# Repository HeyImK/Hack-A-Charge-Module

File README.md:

# Hack-A-Charge IP5306 Charging and Power Board

A compact lithium battery charger and 5V boost module built around the IP5306 chip. It handles charging a single-cell lithium battery via USB-C and boosting the battery voltage up to a stable 5V output for external devices.

## Pictures

| Top View | Bottom View |
| :---: | :---: |
|  |  |

## Features

* **Main Chip:** IP5306 handles both 2.1A battery charging and 2.4A synchronous 5V boosting.
* **Custom 3-LED Layout:** Configured with 3 specific status indicators showing Power Connected, Capacity >25%, and Capacity >75%.
* **Thermal Design:** Uses the ESOP-8 package with the exposed bottom power pad soldered directly to ground vias for cooling.
* **5V Output:** Solid 5V power line capable of supplying up to 2.1A to drive microcontrollers, displays, or peripherals.
* **Battery Connector:** Standard right-angle 2-pin JST-XH socket keeping the battery wire connection flat and low-profile.

## Core Components Used

* **Power Management IC:** Injoinic IP5306 
* **Power Inductor:** SWPA6045S1R0NT (1.0µH, 5.6A saturation current, 6x6x4.5mm SMD package)
* **Spike Filter:** Murata 0.1µF 50V X7R 0603 Ceramic Cap.
* **Indicators:** 0805 LEDs of different colours with 1kΩ resistors

| Circuit Schematic Design |
| :---: |
|  |

| PCB Top Layer Routing | PCB Bottom Layer Routing |
| :---: | :---: |
|  |  |

### Connections
* **5V_OUT** 5V Output (at near 2.1 Amps) from the ip5306 in-built boost circuit.
* **BATT_CONN** The connector to connect the battery with the pcb for charging and output.
* **ACTV_BTN** For manual ON/OFF control and forced shut down and to check battery percentage when needed.

## License

This hardware project is open-source and licensed under the CERN Open Hardware Licence Version 2 - Strongly Reciprocal (CERN-OHL-S-2.0). 

You are free to copy, modify, distribute, and manufacture this board for personal or commercial use. However, if you modify these schematic or layout files and distribute your new design, you must release those modifications under this exact same CERN-OHL-S-2.0 license.

This design is shared without any warranty or implied guarantee. Check the LICENSE file for the full legal text.

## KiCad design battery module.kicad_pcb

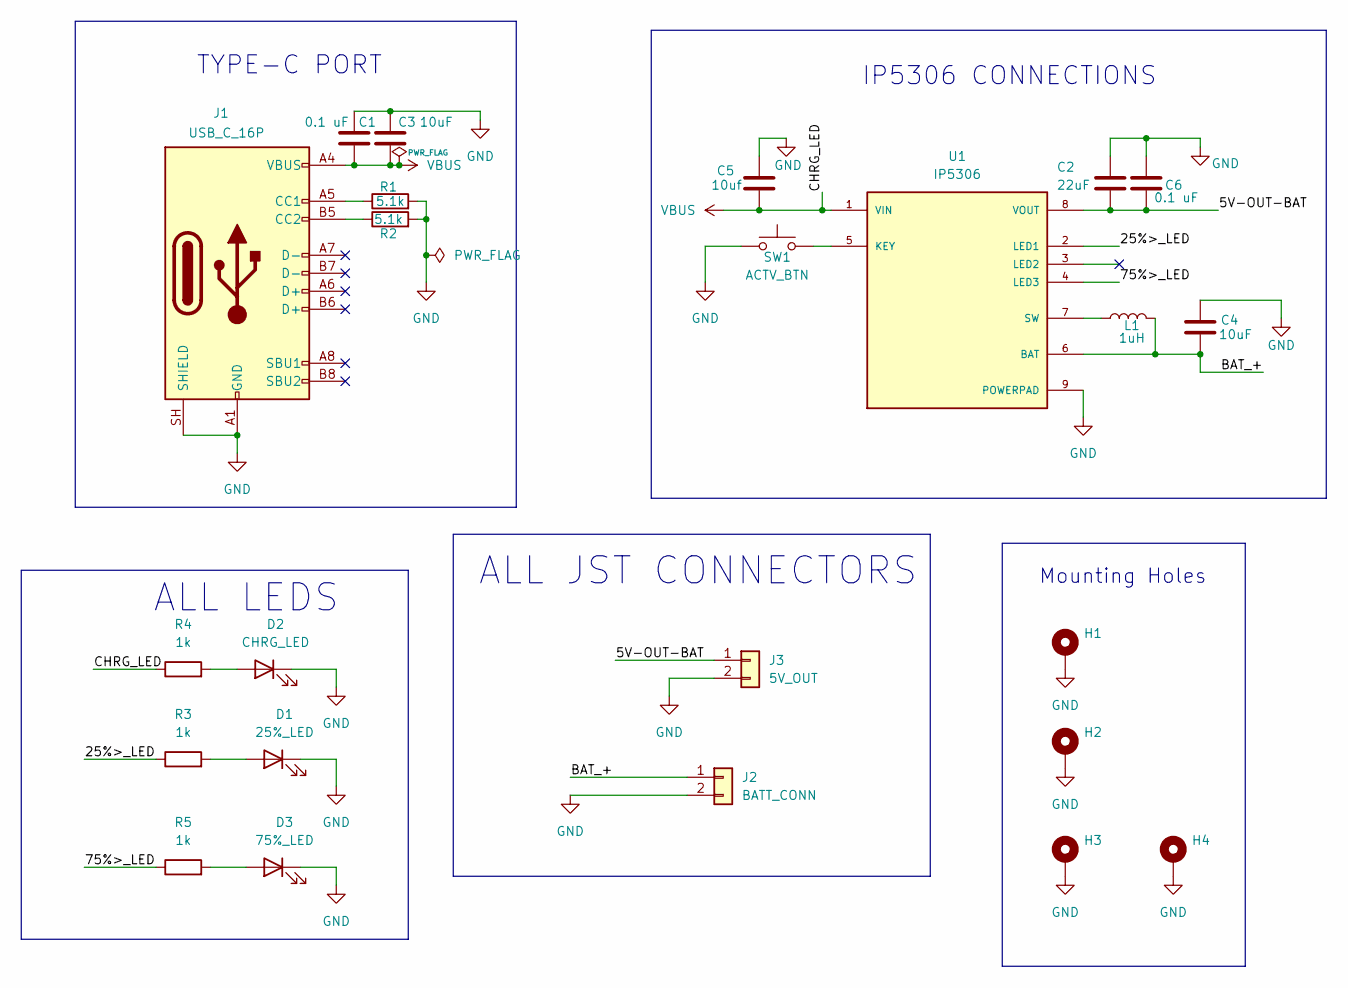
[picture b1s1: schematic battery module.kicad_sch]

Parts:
C1, C6: 0.1 uF; C_0603_1608Metric
C2: 22uF
C3, C4: 10uF
C5: 10uf
D1: 25%_LED; LED_0805_2012Metric
D2: CHRG_LED; LED_0805_2012Metric
D3: 75%_LED; LED_0805_2012Metric
H1, H2, H3, H4: Mount; MountingHole_2.2mm_M2_Pad
J1: USB_C_16P; USB_C_Receptacle_HRO_TYPE-C-31-M-12
J2: BATT_CONN; JST_PH_S2B-PH-K_1x02_P2.00mm_Horizontal
J3: 5V_OUT; JST_PH_S2B-PH-K_1x02_P2.00mm_Horizontal
L1: 1uH
R1, R2: 5.1k; R_0603_1608Metric
R3, R4, R5: 1k; R_0603_1608Metric
SW1: ACTV_BTN; SW_SPST_EVQP2_ShortPushTravel_H2.1mm
U1: IP5306; SOP127P600X165-9N; PARTREV 1.31

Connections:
/5V-OUT-BAT: C2.2, C6.2, J3.1, U1.8 (VOUT)
/25%>_LED: R3.1, U1.2 (LED1)
/75%>_LED: R5.1, U1.4 (LED3)
/BAT_+: C4.2, J2.1, L1.2, U1.6 (BAT)
GND: C1.1, C2.1, C3.1, C4.1, C5.1, C6.1, D1.1 (K), D2.1 (K), D3.1 (K), H1.1 (1_1), H2.1 (1_1), H3.1 (1_1), H4.1 (1_1), J1.A1 (GND), J1.A12 (GND), J1.B1 (GND), J1.B12 (GND), J1.SH (SHIELD), J2.2, J3.2, R1.2, R2.2, SW1.1, U1.9 (POWERPAD); also elsewhere on the board
unnamed: D1.2 (A), R3.2
unnamed: D2.2 (A), R4.2
unnamed: D3.2 (A), R5.2
unnamed 8: J1.A5 (CC1), R1.1; also elsewhere on the board
unnamed 9: J1.B5 (CC2), R2.1; also elsewhere on the board
unnamed: SW1.2, U1.5 (KEY)
unnamed: L1.1, U1.7 (SW)
VBUS: C1.2, C3.2, C5.2, J1.A4 (VBUS), J1.A9 (VBUS), J1.B4 (VBUS), J1.B9 (VBUS), R4.1, U1.1 (VIN); also elsewhere on the board

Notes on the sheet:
ALL JST CONNECTORS
Mounting Holes
ALL LEDS
IP5306 CONNECTIONS
TYPE-C PORT

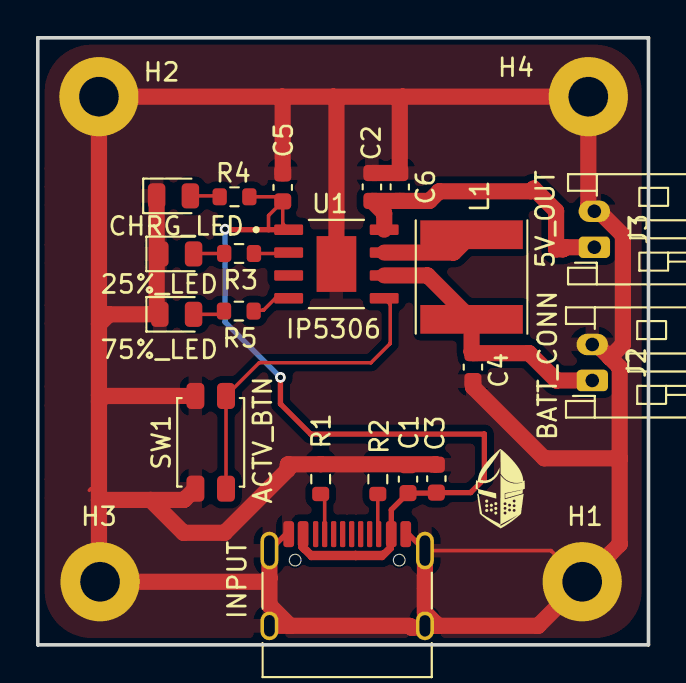
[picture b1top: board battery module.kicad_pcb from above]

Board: 2 copper layers, 33.9 x 33.7 mm, 24 parts (0 on the bottom side), 13 nets.

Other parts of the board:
INPUT: USB_C_16P; USB_C_Receptacle_HRO_TYPE-C-31-M-12

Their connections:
GND: INPUT.A1 (GND), INPUT.A12 (GND), INPUT.B1 (GND), INPUT.B12 (GND), INPUT.SH (SHIELD); also elsewhere on the board
unnamed 8: INPUT.A5 (CC1); also elsewhere on the board
unnamed 9: INPUT.B5 (CC2); also elsewhere on the board
VBUS: INPUT.A4 (VBUS), INPUT.A9 (VBUS), INPUT.B4 (VBUS), INPUT.B9 (VBUS); also elsewhere on the board

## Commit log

2026-06-18 Change license to CERN-OHL-S-2.0
2026-06-26 Revise README title and core components list
    Updated the project title and simplified component descriptions in the README.
